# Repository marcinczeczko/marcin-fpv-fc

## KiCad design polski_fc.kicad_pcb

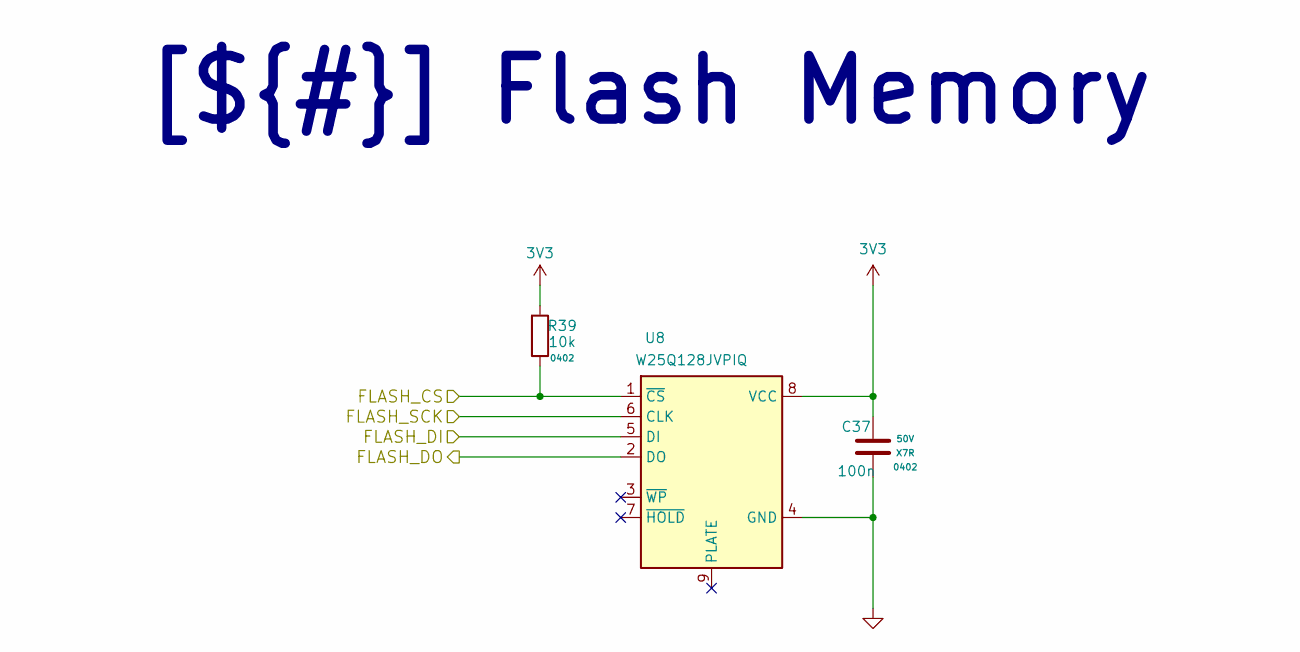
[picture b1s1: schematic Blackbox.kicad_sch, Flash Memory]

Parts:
C37: 100n; C_0402; Voltage 50V; MANUFACTURER # GRM155R71H104KE14D; LCSC C77020
R39: 10k; R_0402; MANUFACTURER # RC0402FR-0710KL; LCSC C60490
U8: W25Q128JVPIQ; SON127P500X600X80-9N; MANUFACTURER # W25Q128JVPIQ; LCSC C190862

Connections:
3V3: C37.1, R39.1, U8.8 (VCC); also elsewhere on the board
/Project Architecture/Blackbox/FLASH_CS: R39.2, U8.1 (~CS); also elsewhere on the board
/Project Architecture/Blackbox/FLASH_DI: U8.5 (DI); also elsewhere on the board
/Project Architecture/Blackbox/FLASH_DO: U8.2 (DO); also elsewhere on the board
/Project Architecture/Blackbox/FLASH_SCK: U8.6 (CLK); also elsewhere on the board
GND: C37.2, U8.4 (GND); also elsewhere on the board

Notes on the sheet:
[${#}] ${TITLE}

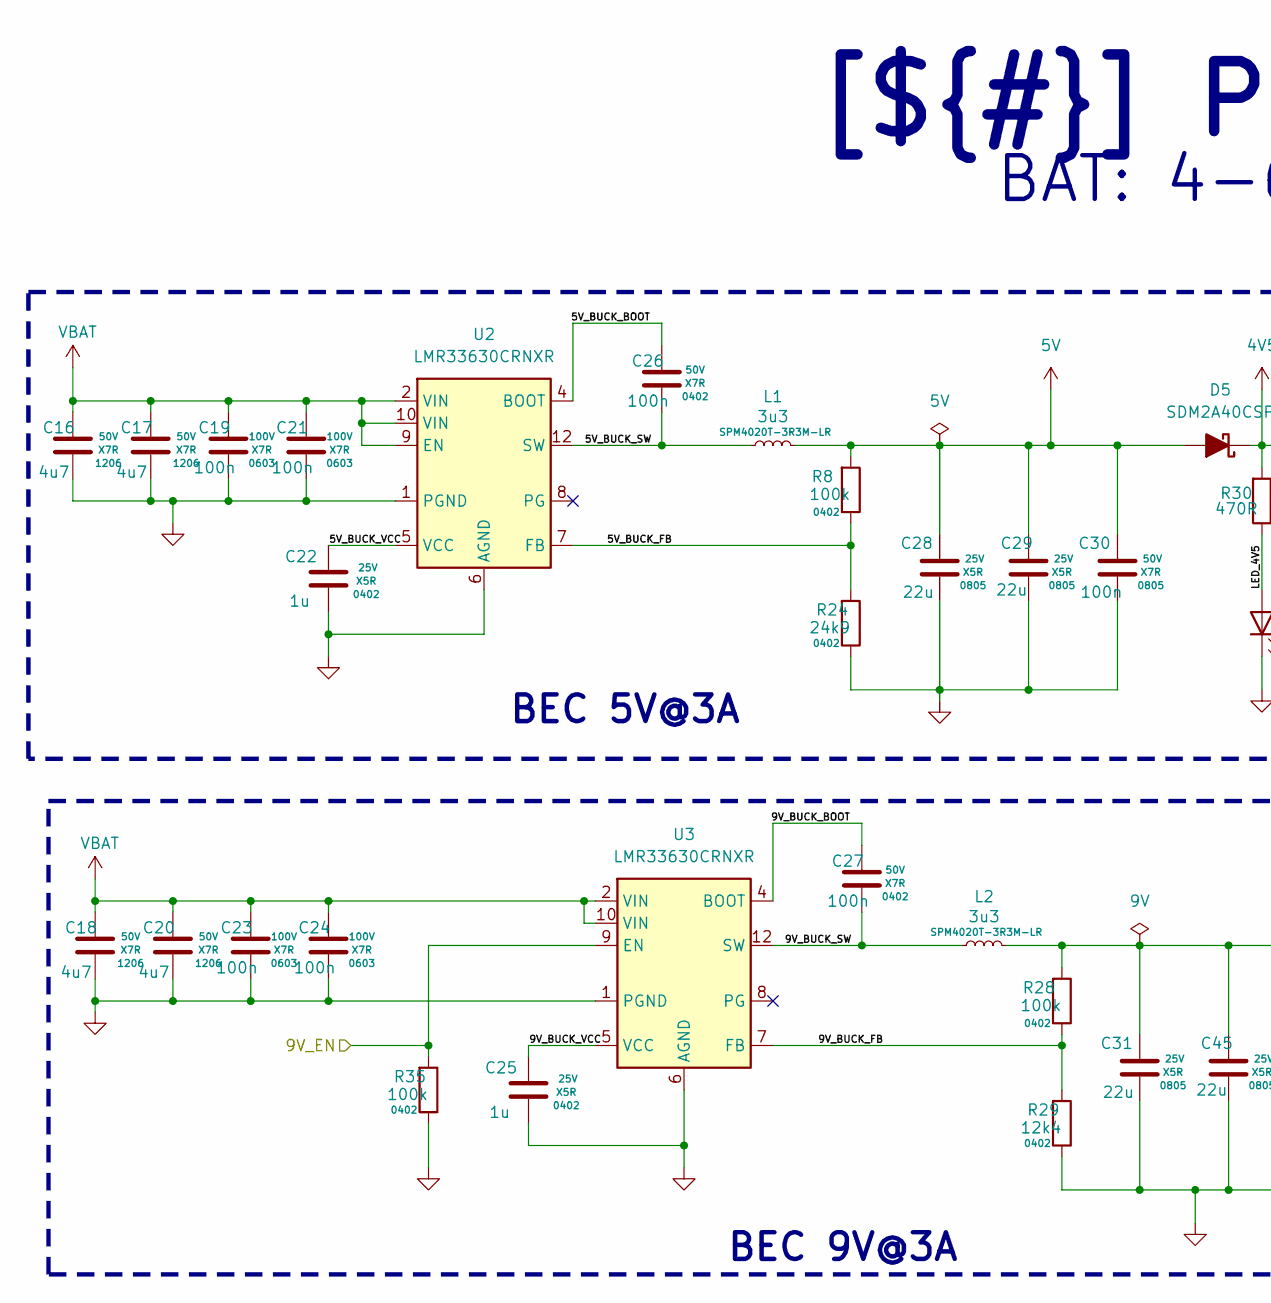
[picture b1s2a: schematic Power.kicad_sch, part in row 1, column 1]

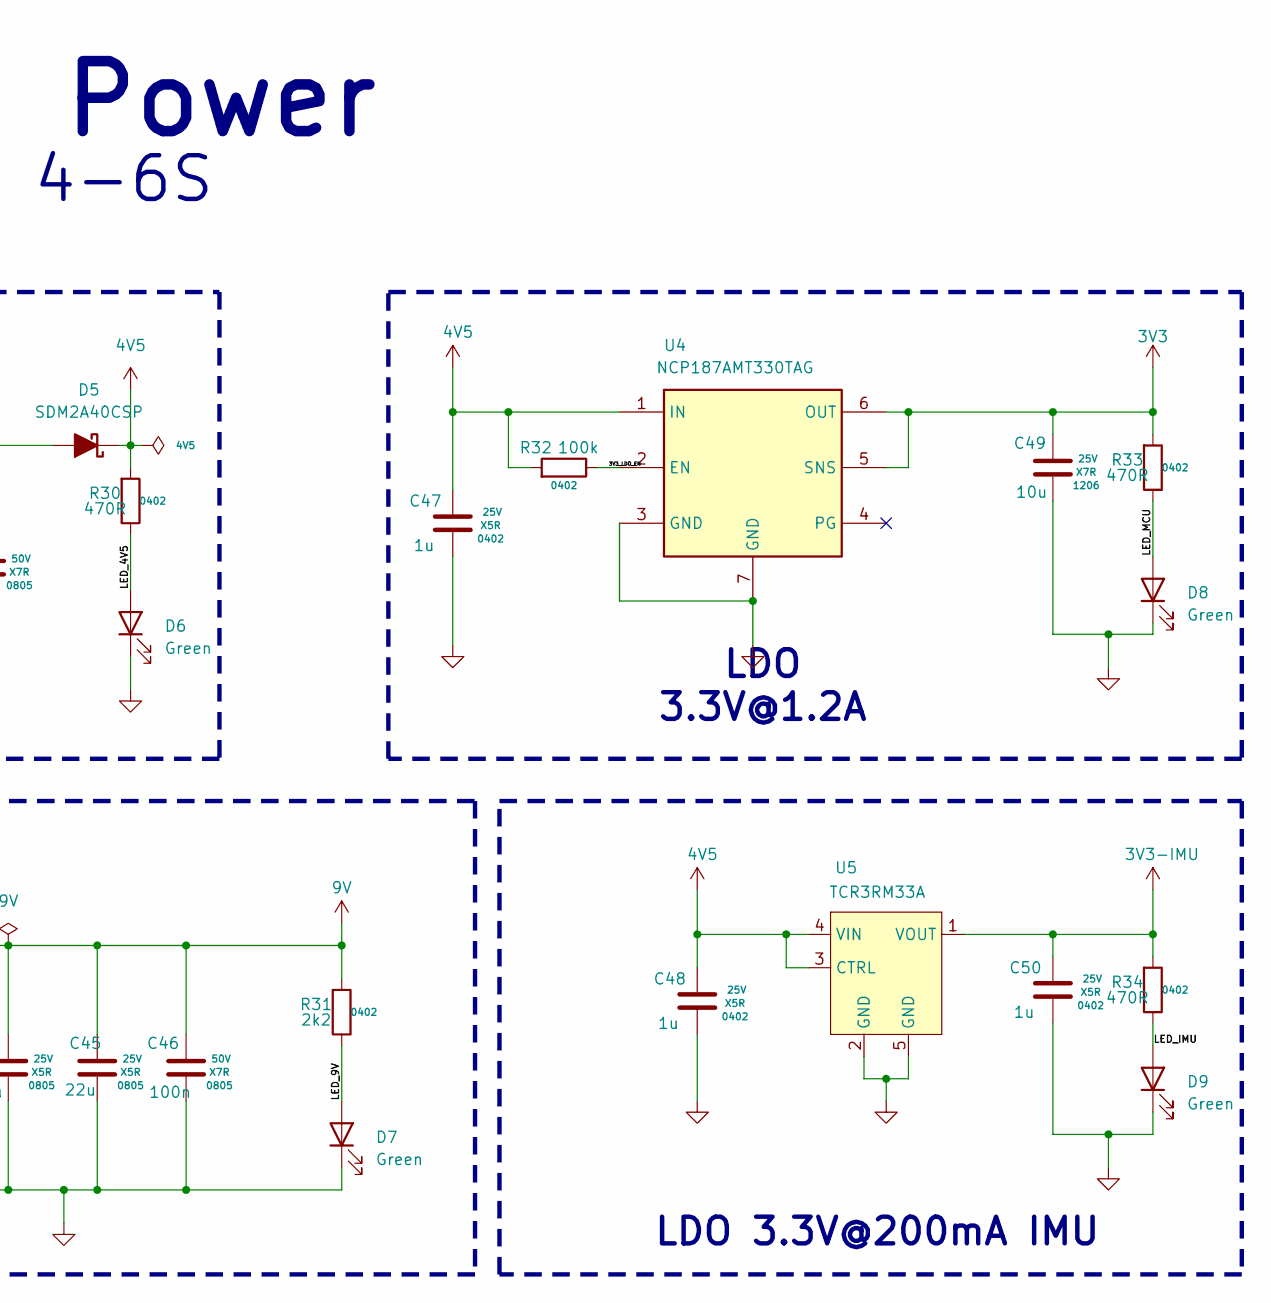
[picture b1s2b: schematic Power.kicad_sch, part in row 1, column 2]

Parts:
C16, C17, C18, C20: 4u7; C_1206; Voltage 50V; MANUFACTURER # GRM31CR71H475KA12L; LCSC C437568
C19, C21, C23, C24: 100n; C_0603; Voltage 100V; MANUFACTURER # GRM188R72A104KA35D; LCSC C161262
C22, C25, C47, C48, C50: 1u; C_0402; Voltage 25V; MANUFACTURER # GRM155R61E105KA12D; LCSC C77009
C26, C27: 100n; C_0402; Voltage 50V; MANUFACTURER # GRM155R71H104KE14D; LCSC C77020
C28, C29, C31, C45: 22u; C_0805; Voltage 25V; MANUFACTURER # GRM21BR61E226ME44L; LCSC C86816
C30, C46: 100n; C_0805; Voltage 50V; MANUFACTURER # GRM21BR71H104KA01L; LCSC C77082
C49: 10u; C_1206; Voltage 25V; MANUFACTURER # GRM31CR71E106KA12L; LCSC C77093
D5: SDM2A40CSP; SDM2A40CSP7B; MANUFACTURER # SDM2A40CSP-7B; LCSC C6671609
D6, D7, D8, D9: Green; LED_0402; MANUFACTURER # LTST-C281KGKT-5A; LCSC C364551
L1, L2: 3u3; IND_SPM4020T-3R3M-LR; MANUFACTURER # SPM4020T-3R3M-LR; LCSC C494329
R8, R28, R32, R35: 100k; R_0402; MANUFACTURER # RP0402BRD07100KL; LCSC C7294193
R24: 24k9; R_0402; MANUFACTURER # RP0402BRD0724K9L; LCSC C7294197
R29: 12k4; R_0402; MANUFACTURER # AT0402BRD0730K1L; LCSC C850952
R30, R33, R34: 470R; R_0402; MANUFACTURER # RC0402FR-07470RL; LCSC C114877
R31: 2k2; R_0402; MANUFACTURER # RC0402FR-072K2L; LCSC C114762
U2, U3: LMR33630CRNXR; MANUFACTURER # LMR33630CRNXR; LCSC C2071783
U4: NCP187AMT330TAG; NCP187x-WDFNW6_2x2_0.65P; MANUFACTURER # NCP187AMT330TAG; LCSC C892299
U5: TCR3RM33A; TCR3RMx-DFN4F_TOS; MANUFACTURER # TCR3RM33A,LF(SE; LCSC C5797528

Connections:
3V3: C49.1, R33.1, U4.5 (SNS), U4.6 (OUT); also elsewhere on the board
3V3-IMU: C50.1, R34.1, U5.1 (VOUT); also elsewhere on the board
4V5: C47.1, C48.1, D5.1 (K), R30.1, R32.1, U4.1 (IN), U5.3 (CTRL), U5.4 (VIN); also elsewhere on the board
5V: C28.1, C29.1, C30.1, D5.2 (A), L1.2, R8.1; also elsewhere on the board
9V: C31.1, C45.1, C46.1, L2.2, R28.1, R31.1; also elsewhere on the board
/Project Architecture/MCU/VTX_EN: R35.1, U3.9 (EN); also elsewhere on the board
/Project Architecture/Power/3V3_LDO_EN: R32.2, U4.2 (EN)
/Project Architecture/Power/5V_BUCK_BOOT: C26.1, U2.4 (BOOT)
/Project Architecture/Power/5V_BUCK_FB: R8.2, R24.1, U2.7 (FB)
/Project Architecture/Power/5V_BUCK_SW: C26.2, L1.1, U2.3 (NC), U2.12 (SW)
/Project Architecture/Power/5V_BUCK_VCC: C22.1, U2.5 (VCC)
/Project Architecture/Power/9V_BUCK_BOOT: C27.1, U3.4 (BOOT)
/Project Architecture/Power/9V_BUCK_FB: R28.2, R29.1, U3.7 (FB)
/Project Architecture/Power/9V_BUCK_SW: C27.2, L2.1, U3.3 (NC), U3.12 (SW)
/Project Architecture/Power/9V_BUCK_VCC: C25.1, U3.5 (VCC)
/Project Architecture/Power/LED_4V5: D6.2 (A), R30.2
/Project Architecture/Power/LED_9V: D7.2 (A), R31.2
/Project Architecture/Power/LED_IMU: D9.2 (A), R34.2
/Project Architecture/Power/LED_MCU: D8.2 (A), R33.2
GND: C16.2, C17.2, C18.2, C19.2, C20.2, C21.2, C22.2, C23.2, C24.2, C25.2, C28.2, C29.2, C30.2, C31.2, C45.2, C46.2, C47.2, C48.2, C49.2, C50.2, D6.1 (K), D7.1 (K), D8.1 (K), D9.1 (K), R24.2, R29.2, R35.2, U2.1 (PGND), U2.6 (AGND), U2.11 (PGND), U3.1 (PGND), U3.6 (AGND), U3.11 (PGND), U4.3 (GND), U4.7 (GND), U5.2 (GND), U5.5 (GND); also elsewhere on the board
VBAT: C16.1, C17.1, C18.1, C19.1, C20.1, C21.1, C23.1, C24.1, U2.2 (VIN), U2.9 (EN), U2.10 (VIN), U3.2 (VIN), U3.10 (VIN); also elsewhere on the board

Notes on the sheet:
[${#}] ${TITLE}
BEC 5V@3A
BAT: 4-6S
LDO 3.3V@200mA IMU
BEC 9V@3A
LDO 3.3V@1.2A

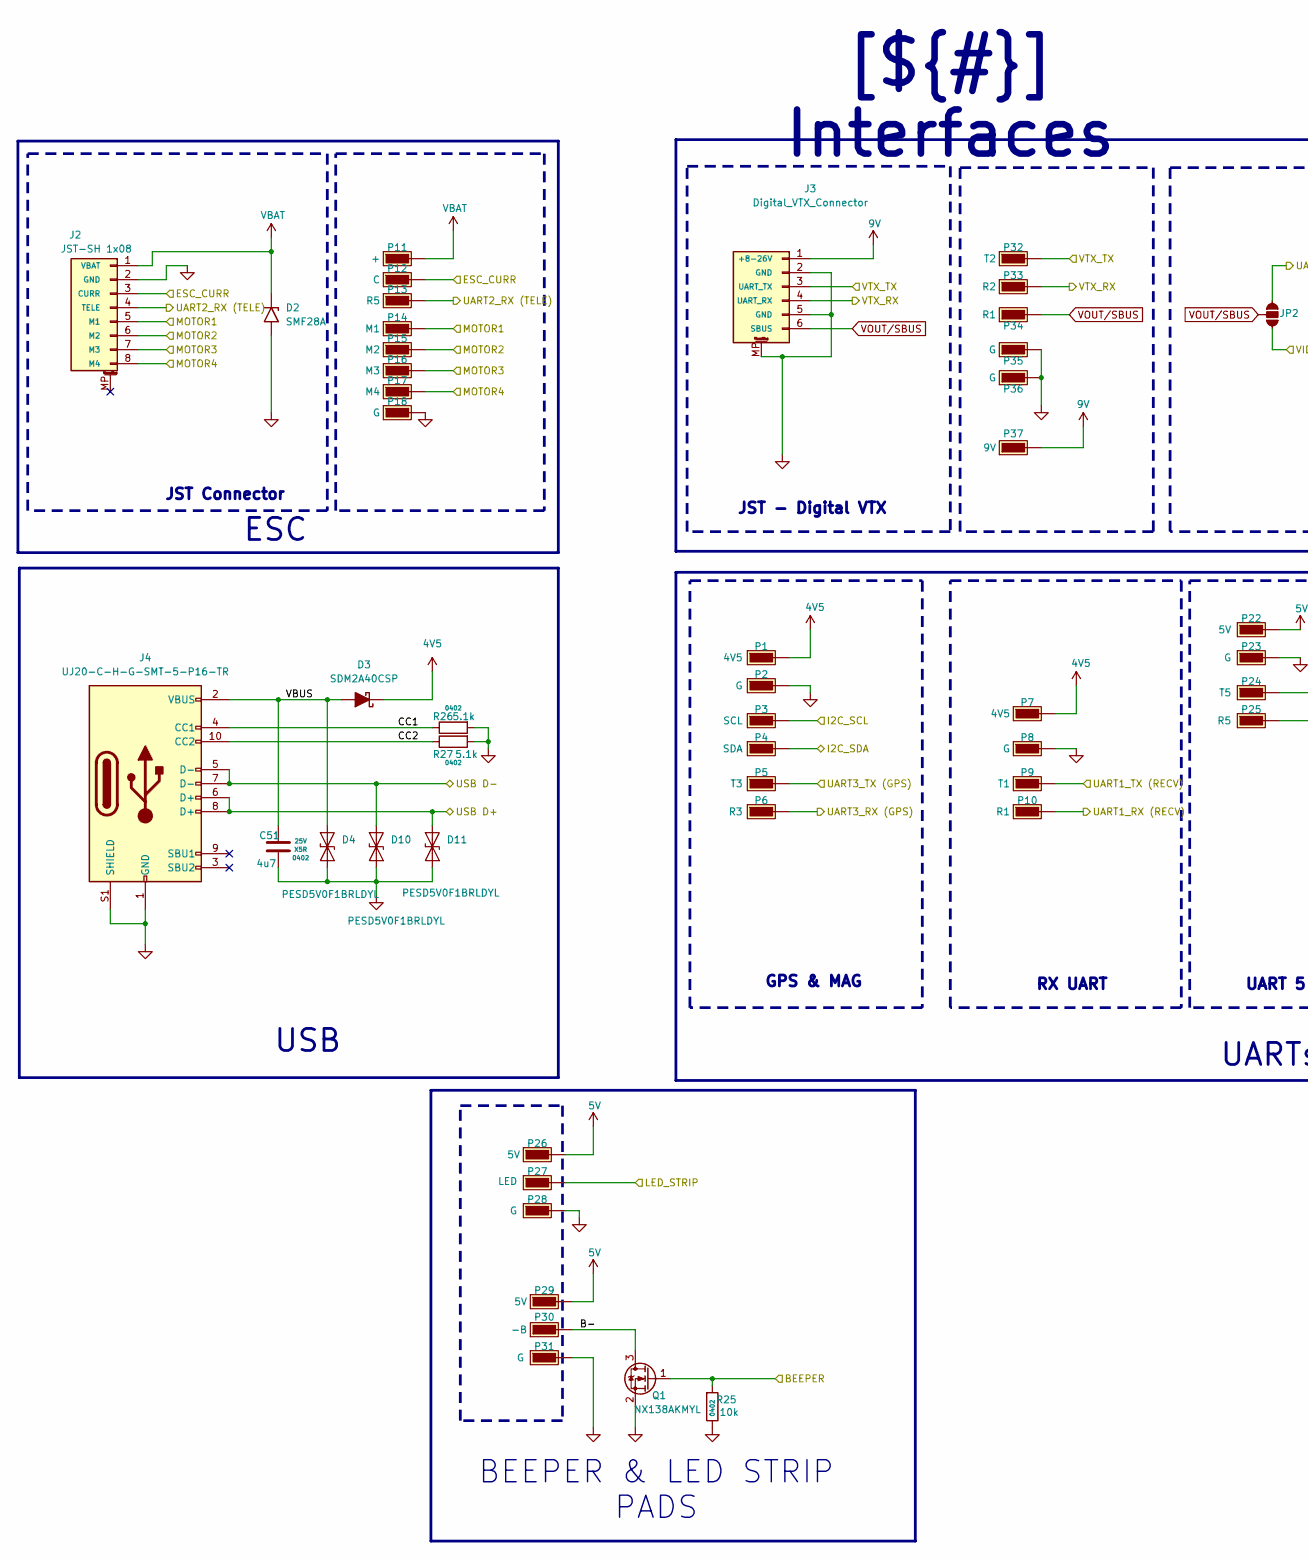
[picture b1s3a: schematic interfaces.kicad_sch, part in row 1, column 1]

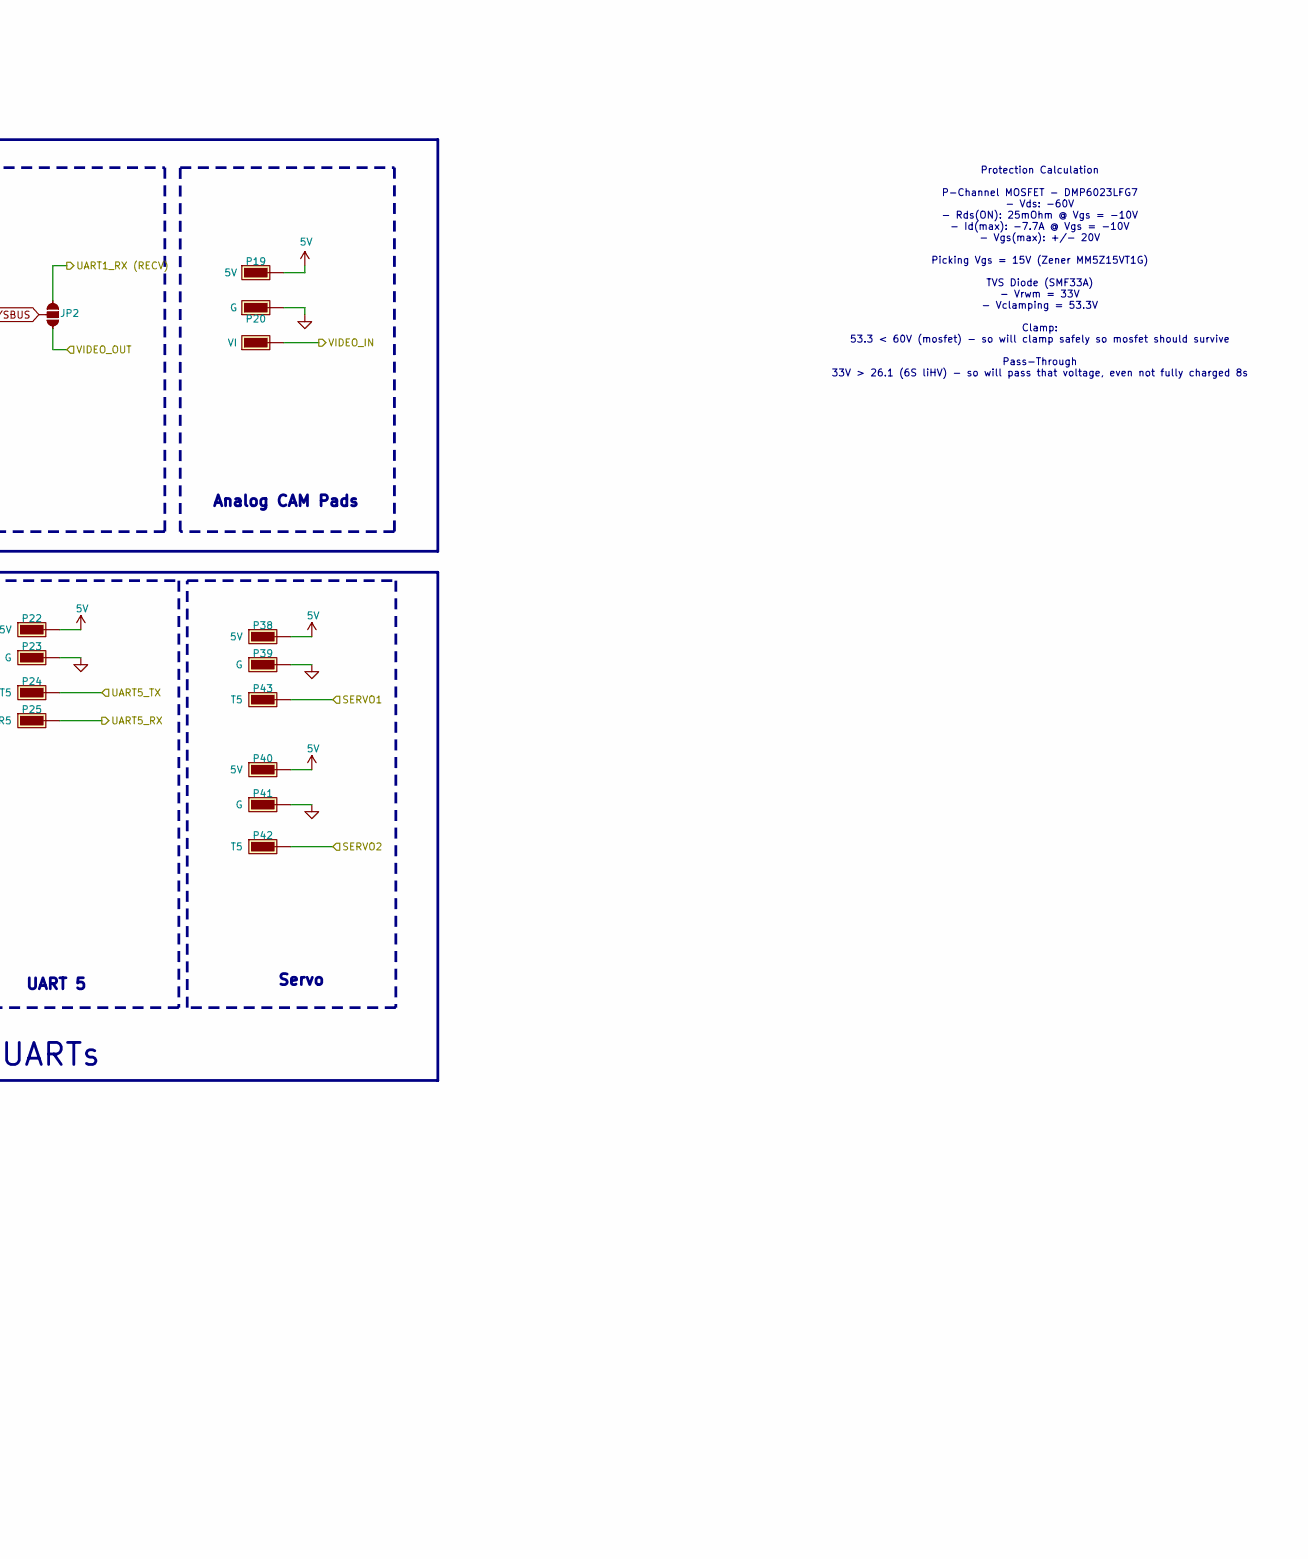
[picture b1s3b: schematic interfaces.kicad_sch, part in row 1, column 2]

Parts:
C51: 4u7; C_0402; Voltage 25V; MANUFACTURER # GRM155R61C475KE15D; LCSC C426094
D2: SMF28A; SMF_DO-219AB; MANUFACTURER # SMF28A-E3-08; LCSC C1973133
D3: SDM2A40CSP; SDM2A40CSP7B; MANUFACTURER # SDM2A40CSP-7B; LCSC C6671609
D4, D10, D11: PESD5V0F1BRLDYL; PESD5V0S1BL315; MANUFACTURER # PESD5V0F1BRLDYL; LCSC C552549
J2: JST-SH 1x08; JST_SH_SM08B-SRSS-TB_1x08-1MP_P1.00mm_Horizontal; MANUFACTURER # HC-1.0-8PWT; LCSC C2845367
J3: Digital_VTX_Connector; JST-SH_SM06BSRSSTBLFSN; MANUFACTURER # SM06B-SRSS-TB(LF)(SN); LCSC C160405
J4: UJ20-C-H-G-SMT-5-P16-TR; SAMESKY_UJ20-C-H-G-SMT-5-P16-TR; MANUFACTURER # UJ20-C-H-G-SMT-5-P16-TR; MOUSER # 179-UJ20CHGSMT5P16TR
JP2: SolderJumper-3_Open_TrianglePad1.0x1.5mm
P1, P7: 4V5; FC_SolderPad_4_no_hole
P2, P8, P18, P20, P23, P28, P31, P35, P36, P39, P41: G; FC_SolderPad_4_no_hole
P3: SCL; FC_SolderPad_4_no_hole
P4: SDA; FC_SolderPad_4_no_hole
P5: T3; FC_SolderPad_4_no_hole
P6: R3; FC_SolderPad_4_no_hole
P9: T1; FC_SolderPad_4_no_hole
P10, P34: R1; FC_SolderPad_4_no_hole
P11: +; FC_SolderPad_4_no_hole
P12: C; FC_SolderPad_4_no_hole
P13, P25: R5; FC_SolderPad_4_no_hole
P14: M1; FC_SolderPad_4_no_hole
P15: M2; FC_SolderPad_4_no_hole
P16: M3; FC_SolderPad_4_no_hole
P17: M4; FC_SolderPad_4_no_hole
P19, P22, P26, P29, P38, P40: 5V; FC_SolderPad_4_no_hole
P21: VI; FC_SolderPad_4_no_hole
P24, P42, P43: T5; FC_SolderPad_4_no_hole
P27: LED; FC_SolderPad_4_no_hole
P30: -B; FC_SolderPad_4_no_hole
P32: T2; FC_SolderPad_4_no_hole
P33: R2; FC_SolderPad_4_no_hole
P37: 9V; FC_SolderPad_4_no_hole
Q1: NX138AKMYL; MANUFACTURER # NX138AKMYL; LCSC C3290147
R25: 10k; R_0402; MANUFACTURER # RC0402FR-0710KL; LCSC C60490
R26, R27: 5.1k; R_0402; MANUFACTURER # AC0402JR-075K1L; LCSC C227396

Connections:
4V5: D3.1 (K), P1.1, P7.1; also elsewhere on the board
5V: P19.1, P22.1, P26.1, P29.1, P38.1, P40.1; also elsewhere on the board
9V: J3.1 (+8-26V), P37.1; also elsewhere on the board
/Project Architecture/IMU & Baro/BARO_I2C_SCL: P3.1; also elsewhere on the board
/Project Architecture/IMU & Baro/BARO_I2C_SDA: P4.1; also elsewhere on the board
/Project Architecture/Interfaces/B-: P30.1, Q1.3 (D)
/Project Architecture/Interfaces/BEEPER: Q1.1 (G), R25.1; also elsewhere on the board
/Project Architecture/Interfaces/CC1: J4.4 (CC1), R26.2
/Project Architecture/Interfaces/CC2: J4.10 (CC2), R27.2
/Project Architecture/Interfaces/ESC_CURR: J2.3 (CURR), P12.1; also elsewhere on the board
/Project Architecture/Interfaces/LED_STRIP: P27.1; also elsewhere on the board
/Project Architecture/Interfaces/MOTOR1: J2.5 (M1), P14.1; also elsewhere on the board
/Project Architecture/Interfaces/MOTOR2: J2.6 (M2), P15.1; also elsewhere on the board
/Project Architecture/Interfaces/MOTOR3: J2.7 (M3), P16.1; also elsewhere on the board
/Project Architecture/Interfaces/MOTOR4: J2.8 (M4), P17.1; also elsewhere on the board
/Project Architecture/Interfaces/SERVO1: P43.1; also elsewhere on the board
/Project Architecture/Interfaces/SERVO2: P42.1; also elsewhere on the board
/Project Architecture/Interfaces/UART1_RX (RECV): JP2.1 (A), P10.1; also elsewhere on the board
/Project Architecture/Interfaces/UART1_TX (RECV): P9.1; also elsewhere on the board
/Project Architecture/Interfaces/UART2_RX (TELE): J2.4 (TELE), P13.1; also elsewhere on the board
/Project Architecture/Interfaces/UART3_RX (GPS): P6.1; also elsewhere on the board
/Project Architecture/Interfaces/UART3_TX (GPS): P5.1; also elsewhere on the board
/Project Architecture/Interfaces/UART5_RX: P25.1; also elsewhere on the board
/Project Architecture/Interfaces/UART5_TX: P24.1; also elsewhere on the board
/Project Architecture/Interfaces/USB D+: D11.1 (A1), J4.6 (D+), J4.8 (D+); also elsewhere on the board
/Project Architecture/Interfaces/USB D-: D10.1 (A1), J4.5 (D-), J4.7 (D-); also elsewhere on the board
/Project Architecture/Interfaces/VBUS: C51.1, D3.2 (A), D4.1 (A1), J4.2 (VBUS), J4.11 (VBUS)
/Project Architecture/Interfaces/VIDEO_IN: P21.1; also elsewhere on the board
/Project Architecture/Interfaces/VIDEO_OUT: JP2.3 (C); also elsewhere on the board
/Project Architecture/Interfaces/VTX_RX: J3.4 (UART_RX), P33.1; also elsewhere on the board
/Project Architecture/Interfaces/VTX_TX: J3.3 (UART_TX), P32.1; also elsewhere on the board
GND: C51.2, D2.2 (A2), D4.2 (A2), D10.2 (A2), D11.2 (A2), J2.2 (GND), J3.2 (GND), J3.5 (GND), J3.MP, J4.1 (GND), J4.12 (GND), J4.S1 (SHIELD), J4.S2 (SHIELD), J4.S3 (SHIELD), J4.S4 (SHIELD), P2.1, P8.1, P18.1, P20.1, P23.1, P28.1, P31.1, P35.1, P36.1, P39.1, P41.1, Q1.2 (S), R25.2, R26.1, R27.1; also elsewhere on the board
VBAT: D2.1 (A1), J2.1 (VBAT), P11.1; also elsewhere on the board
VOUT/SBUS: J3.6 (SBUS), JP2.2 (B), P34.1

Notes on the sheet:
BEEPER & LED STRIP PADS
Protection Calculation P-Channel MOSFET - DMP6023LFG7 - Vds: -60V - Rds(ON): 25mOhm @ Vgs = -10V - Id(max): -7.7A @ Vgs = -10V - Vgs(max): +/- 20V Picking Vgs = 15V (Zener MM5Z15VT1G) TVS Diode (SMF33A) - Vrwm = 33V - Vclamping = 53.3V Clamp: 53.3 < 60V (mosfet) - so will clamp safely so mosfet sho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
RX UART
JST - Digital VTX
Servo
[${#}] ${TITLE}
GPS & MAG
USB
UARTs
JST Connector
UART 5
ESC
Analog CAM Pads
